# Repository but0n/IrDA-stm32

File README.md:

# 1. 绪论

## 1.1 红外遥控的发展

二十世纪, 刚步入八十年代, 电视产品在日本快速发展, 相应的红外遥控技术也在这里得到了广泛应用。为了实现遥控码的发射, 他们使用了一种集成发射芯片, 这种芯片的特点是: 单一控制（内部预置固定编码的遥控器只能控制单一型号的电器）。

随着时代不断地进步, 在目前的日常家居生活里面, 一般家庭都会配置各种各样的家用电器, 相应的也会有各种各样的遥控器, 当需要遥控某一家用电器时, 需要从多个遥控器中选出特定的一个。当家用电器越来越多, 对应的遥控器也越来越多, 从众多的遥控器中选出所需要的遥控器也会更加麻烦, 过多的遥控器会占据相当一部分的家居空间, 也不方便整理。

针对这种情况, 人们便产生了一种想法: 是否可以用一只遥控器遥控所有家用电器[5]？答案是肯定的, 多用遥控器就此产生了, 这种遥控器的特点是: 遥控器里面预置了不止一套编码, 而是多套编码, 可供用户在不同场合选择不同模式。

伴随着科技的日新月异, 红外遥控技术和单片机技术已经越来越成熟, 嵌入式技术的大力发展, 使大部分商家都在生产一种新的遥控器: 这种遥控器内置一个动态的编码库, 库内存放用户自主录入的编码, 使其具备一中心的功能——红外学习功能, 这种遥控器也有了新的名称: 学习型红外遥控器。

## 1.2 红外通信原理概述

所谓红外通信, 就是通过对二进制数字的调节与调制, 来进行信号传输, 红外通信接口就是红外信道的调制解调器。利用红外技术, 实现两点间的近距离保密通信和信息转发, 称为红外通信。它一般由两部分组成, 即: 红外发射系统与红外接收系统。单片机本身并不具备红外通信接口, 我们可以利用红外发射电路与红外接收电路组成一个应用于单片机的红外通信接口。

红外通信的基本原理是通过红外发射管发射的将基带二进制信号调制为一系列的脉冲串信号载波信号。

在红外通信过程中调制和发送的数据共有三种常用的协议:

 - NEC协议
 - 夏普协议
 - 索尼SIRC协议

其中应用最广泛的是NEC协议。NEC标准规定: 红外通信的载波频率为38KHz, 占空比为1: 3；数据格式包括了引导码、用户码、数据码和数据码反码, 编码总占 32 位。数据反码是 数据码反相后的编码, 编码时可用于对数据的纠错。注意: 第二段的用户码也可以在遥控应用电路中被设置成第一段用户码的反码, 如下图所示:

## 1.3 通用红外通信设备学码的实现

通用红外通信设备按照学习方式的不同可以分为两类:

 - 固定码格式的通信设备
 - 波形拷贝式的通信设备

第一种通信设备需要收集保存不同种类的红外设备信号, 然后识别比较, 最后再记录。这种红外设备的优点是硬件要求相对简易, 控制器的CPU频率可以较低；缺点是因为红外编码格式太多, 实现红外设备的成功复制比较难。

第二种通信设备是把原来红外设备发出的信号进行完全的复制, 不管原来红外设备红外信号是什么格式, 然后存储到非易失性的存储器(如EEPROM)中, 发送时再把保存的波形数据取出, 还原成原始信号。其优点是可以对任何一种红外设备进行学习；缺点是对控制器CPU的频率要求较高, RAM要大。
为了对尽可能多的设备进行控制, 本设计完成的是第二种红外通信设备。

# 2. 红外学码系统电路设计

上图是该硬件系统的完整电路图, 该电路共分为 7 个部分:

 1. 稳压电源电路
 2. 单片机启动配置电路
 3. 单片机外部时钟晶振电路
 4. 单片机上电复位电路
 5. 8 路学码部分电路
 6. 8 路发码部分电路
 7. 电路板接口电路

## 2.1 稳压电源电路

稳压电源电路是用来将外部供电电源的电压转换成单片机所需的 3.3V 稳定的电压。

这里使用了型号为 XC6206P332MR 的稳压 LDO 芯片, LDO即 Low Dropout Regulator, 是一种低压差线性稳压器。并且在芯片的电源输入引脚和电源输出引脚分别接了两个滤波电容, 用来防止电源可能发生的波动, 提高数字电路工作的稳健性。

上图是该 LDO 芯片型号为 P302MR 的典型输入输出电压曲线, 横轴为输入电压, 纵轴为输出电压, 通过上图可以清楚的看出, 我们所使用的 P332MR 当输入电压在 3.4V ~ 6V 的范围内, 都可以输出稳定的 3.3V 电压。

(这张图表是XC6206P302的数据, 官方的数据手册中只有该型号的图表作为一个典型示例, 没有我们所使用的 P332MR, 所以图表中的输出电压不是3.3V)

## 2.2 单片机启动配置电路

在STM32F10xxx里, 可以通过BOOT[1: 0]引脚选择三种不同启动模式:

- 从主闪存存储器启动:  主闪存存储器被映射到启动空间 (0x0000 0000), 但仍然能够在它原
有的地址 (0x0800 0000) 访问它, 即闪存存储器的内容可以在两个地址区域访问, 0x0000
0000 或 0x0800 0000。
> **以这种模式启动会运行用户烧写的程序**

- 从系统存储器启动: 系统存储器被映射到启动空间 (0x0000 0000), 但仍然能够在它原有的
地址(互联型产品原有地址为 0x1FFF B000, 其它产品原有地址为0x1FFF F000)访问它。
> **以这种模式启动会运行单片机出厂自带的 ISP 程序(In System Program 在系统编程), 这时我们可以通过串口连接单片机来上传程序。**

在系统复位后, SYSCLK 的第4个上升沿, BOOT 引脚的值将被锁存。用户可以通过设置 BOOT1
 和 BOOT0 引脚的状态, 来选择在复位后的启动模式。

在这次设计中, 我们将 BOOT1 通过一个 10K 的限流电阻直接接地, 通过 BOOT0 来控制单片机的启动模式。在实际使用的过程中, 单片机默认会以第一种模式启动 (BOOT0 悬空时为低电平), 也就是运行用户的程序, 如果我们要烧写程序, 只需要在单片机供电时确保 BOOT0 为高电平, 如下图, 将电阻 R3 右侧短接上方电容 C7 左侧即可。

## 2.3 单片机外部时钟晶振电路

4~16Mz外部振荡器可为系统提供更为精确的主时钟, 在这里单片机的高速外部时钟信号 (HSE) 是由以下一个8Mhz晶振产生的。
晶振两个引脚分别连接单片机的外部时钟引脚, 并且连接了两个 20pF 的负载电容, 作用是对晶体和振荡电路的补偿和匹配, 使电路易于起振并处于合理的激励态下, 同时对振荡频率也有一定的微调作用; 同时晶振也并联了一个 1M 欧的电阻 R2, 起到分流作用, 使晶振的工作电流在一个合理的范围内。

## 2.4 单片机上电复位电路

STM32 支持三种复位形式, 分别为系统复位、上电复位和备份区域复位, 这里的电路图属于上电复位。

芯片内部的复位信号源是单片机的 NRST 引脚, 脉冲发生器保证每一个(外部或内部)复位源都能有
至少20μs的脉冲延时; 当 NRST 引脚被拉低产生外部复位时, 它将产生复位脉冲, 然后单片机将会复位除了备份区域外的所有寄存器, 也就是清除上次运行后单片机配置可能发生的改变, 目的是让系统回到一个固定的初始状态, 这时所有寄存器的值都是已知的, 所以在这之后对单片机的每一次操作的结果都是可以判断的。

上图是单片机的上电复位电路, RESET 连接在单片机的 NRST 引脚, 在电路板开始供电时电容 C9 两侧是短路的, 也就是说这时 RESET 是直接接地的, 为低电平, 随着时间的推移, 电容将会被上拉的限流电阻 R8 充电, 随后 RESET 到 GND 之间就会形成断路, 这时 RESET 会变为高电平, 在整个过程也就中产生了低电平的复位信号。

## 2.5 8路学码部分电路

上图为 8 路的学码电路, 每一路都连接了一个 VS838 红外接收管:

VS838 的电源管脚 VCC 通过一个限流电阻接电源。

VS838 的 OUT 管脚是信号输出管脚, 当 VS838 接受到红外信号时 OUT 管脚会由高电平变为低电平, 直到红外信号消失。(未收到红外信号时 OUT 脚一直为高电平)

红外信号输出管脚是单片机获取红外信号的唯一来源, 所以该管脚连接在单片机的 GPIO 上, 当收到红外信号时该管脚产生的电平下降沿会被单片机的 GPIO 捕获并产生外部中断, 在中断函数中我们会记录该波形也就是红外信号的波形长度, 从而进行学码。

## 2.6 8路发码部分电路

上图为 8 路的发码电路, NEC标准规定:  红外通信的载波频率为38KHz, 占空比为1: 3,

这里我们使用单片机定时器的 PWM 输出功能产生所需的 38KHz 1: 3 波形, 通过对 PWM 输出的打开和关闭来实现载波。PWM 信号管脚通过一个限流电阻连接一个 NPN 三极管的, 通过控制三极管来打开和关闭红外 LED 进行红外信号的发送。

PWM 信号分别由单片机 TIM3 的四个通道和 TIM4 的四个通道产生。

## 2.7 电路板接口电路

该电路板的接口共有 4 个针脚:

 - 外部电源供电正极
 - 外部电源供电负极
 - 串口信号线 TX
 - 串口信号线 RX

 串口以其通信电路简单、可靠性高和传输距离远等优点，广泛应用在计算机与外设之间的通信电路中。

在本次设计中的串口有两个作用:
 - 串口控制:  电脑通过串口与电路板连接, 发送指令以控制单片机进行学码和发码操作
 - ISP:  电脑通过串口连接单片机来烧写程序。

# 3. 串口控制的8路学码系统的软件原理

## 3.1 主函数
```c
int main() {
	// 配置中断优先级分组
	NVIC_SetPriorityGrouping(0x07 - NVIC_GROUPING);

	uart_init(72, 115200);	// 初始化串口, 波特率为115200
	irda_init();			// irda初始化
	while(1) {
		// uart_sendStr("Alive~");
		// UART_CR();
		// delay_ms(1000);
	}
	return 0;
}
```
在系统供电之后单片机会进行下面这些操作:
- 配置中断优先级分组
- 串口功能初始化
- 8路红外发码收码系统的初始化
- 死循环, 等待用户的进一步操作

## 3.2 配置中断优先级分组

该系统的主要功能如串口控制、红外信号的捕获都依赖于单片机中的中断功能, 所以在程序启动后我们首先要做的就是单片机中断相关的配置。

STM32单片机使用的 Cortex-M3 内核中搭载了一个中断响应系统, 支持为数众多的系统异常和外部中断。当系统存在多个中断时, 优先级对于中断来说就很关键了, 它会决定一个中断是否能被掩蔽, 以及在未掩蔽的
情况下何时可以响应。优先级的数值越小, 则优先级越高。CM3 支持中断嵌套, 使得高优先级中断
会抢占 (preempt) 低优先级中断。有 3 个系统异常: 复位, NMI 以及硬 fault, 它们有固定的优先
级, 并且它们的优先级号是负数, 从而高于所有其它异常。所有其它异常的优先级则都是可编程的。

为了使抢占机能变得更可控, CM3 还把 256 级优先级按位分成高低两段, 分别称
为抢占优先级和子优先级。

并且在 NVIC 中有一个寄存器是 “应用程序中断及复位控制寄存器” (AIRCR), 它里面有一个位段名为 “优先级组”。该位段的值对每一个优先级可配置的异常都有影响 —— 把其优先级分为 2 个
位段: MSB 所在的位段（左边的）对应抢占优先级, 而 LSB 所在的位段（右边的）对应子优先级。

下图是应用程序中断及复位控制寄存器 (AIRCR) 地址:  0xE000_ED0C 的详细说明

我们所使用的 STM32 单片机的 PRIGROUP 只是用了4bit来表示:

通过上图我们可以得到一个规律, 即 PRIGROUP 的值等于 0x07 - 优先级组别。

在主函数中我们会通过下面这行语句将中断优先级分组设置为3, 在寄存器中:  xxx.y (x 指抢占式优先级, y 指响应式优先级):

```c
#define NVIC_GROUPING	3

NVIC_SetPriorityGrouping(0x07 - NVIC_GROUPING);
```

其中调用了 NVIC_SetPriorityGrouping 函数, 该函数用来设置 AIRCR 寄存器的 PPRIGROUP 位, 该函数的定义位于 STM32 官方的头文件 core_cm3.h 中:

```c
/* \brief  Set Priority Grouping

  The function sets the priority grouping field using the required unlock sequence.
  The parameter PriorityGroup is assigned to the field SCB->AIRCR [10: 8] PRIGROUP field.
  Only values from 0..7 are used.
  In case of a conflict between priority grouping and available
  priority bits (__NVIC_PRIO_BITS), the smallest possible priority group is set.

    \param [in]      PriorityGroup  Priority grouping field.
 */
__STATIC_INLINE void NVIC_SetPriorityGrouping(uint32_t PriorityGroup)
{
	uint32_t reg_value;
	uint32_t PriorityGroupTmp = (PriorityGroup & (uint32_t)0x07);
	// only values 0..7 are used

	reg_value  =  SCB->AIRCR;
	// read old register configuration
	reg_value &= ~(SCB_AIRCR_VECTKEY_Msk | SCB_AIRCR_PRIGROUP_Msk);
	// clear bits to change
	reg_value  =  (reg_value |
		((uint32_t)0x5FA << SCB_AIRCR_VECTKEY_Pos) |
        (PriorityGroupTmp << 8));
	// Insert write key and priorty group
	SCB->AIRCR =  reg_value;
}
```

## 3.3 串口功能初始化

STM32 中的通用同步异步收发器(USART)提供了一种灵活的方法与使用工业标准NRZ异步串行数据格式的
外部设备之间进行全双工数据交换。USART利用分数波特率发生器提供宽范围的波特率选择。
它支持同步单向通信和半双工单线通信，也支持LIN(局部互连网)，智能卡协议和IrDA(红外数据
组织)SIR ENDEC规范，以及调制解调器(CTS/RTS)操作。它还允许多处理器通信。
使用多缓冲器配置的DMA方式，可以实现高速数据通信。

在配置好中断优先级分组后, 会进行单片机 USART1 串口的初始化, 配置其波特率为 115200, 并打开串口中断:

```c
uart_init(72, 115200);	// 初始化串口, 波特率为115200
```

下面是该函数的定义:

```c
void uart_init(unsigned int pclk2, unsigned int bound) {
    float temp;
    unsigned short mantissa;
    unsigned short fraction;
    temp = (float)(pclk2*1000000)/(bound*16);
    mantissa = temp;
    fraction = (temp - mantissa) * 16;
    mantissa <<= 4;
    mantissa += fraction;
    RCC->APB2ENR |= RCC_APB2ENR_IOPAEN;		// 打开 GPIOA 时钟
    RCC->APB2ENR |= RCC_APB2ENR_USART1EN;	// 打开 USART1 时钟

    GPIOA->CRH &= 0xFFFFF00F;				// USART GPIO 引脚配置
    GPIOA->CRH |= 0x000008B0;

    RCC->APB2RSTR |= RCC_APB2RSTR_USART1RST;
    RCC->APB2RSTR &= ~RCC_APB2RSTR_USART1RST;

    USART1->BRR = mantissa;
    USART1->CR1 |= 0x200C;	//设置 UE, TE and RE

    USART1->CR1 |= 1<<8;	//PE 中断使能
    USART1->CR1 |= 1<<5;	//RX 非空中断使能

    USART1->SR;     // 读取 SR 寄存器以将 TXE 和 TE 位清零,(复位值:  0x00C0)

	// SCB->AIRCR &= 0x05FAF8FF;	// AIRCE Key:  0x05FA
	// SCB->AIRCR |= 0x05FA0400;	// Set up group value
	NVIC_EnableIRQ(USART1_IRQn);	// 使能串口中断
	NVIC_SetPriority(USART1_IRQn, 0b1001);//设置其优先级
}
```

该函数会进行下面这些操作:
- 打开 USART1 和 USART1 所使用的 GPIO 的时钟, 由于 STM32 的低功耗设计, 只有在打开时钟后才能操作对应的外设。
- 配置 GPIO 引脚:

	在本次设计中我们使用的串口是全双工模式的, 所以根据上图要求, TX 应该配置为推挽复用输出, RX 应该配置为浮空输入或上拉输入。其中 GPIO 引脚的配置需要操作 CRL 或 CRH 寄存器, 下图是该寄存器的说明:

	通过上表我们可以看到, 推挽复用输出的值为 0b1000 (0x8), 上拉输入的值为 0b1011 (0xB), 所以就有了下面这两行配置代码:
	```c
	GPIOA->CRH &= 0xFFFFF00F;				// USART GPIO 引脚配置
	GPIOA->CRH |= 0x000008B0;
	```
- 复位并配置串口1相关寄存器
- 使能单片机的串口中断, 当单片机收到用户从电脑发送的字符后,  会触发串口中断并执行下面的中断处理函数 USART1_IRQHandler :

```c
void USART1_IRQHandler(void) {
	if(USART1->SR & USART_SR_RXNE) {
		const char cmd = USART1->DR;	// 读取串口接收寄存器来清除 RXNE 标志
		switch (cmd) {
			case 0x0D: 	//回车键
			case 0x0A:
				uart_sendStr("\n\r当前命令: \t");
				uart_sendStr(gCmdCache);
				UART_CR();
				uart_decode(gCmdCache);
				clrCache();
				break;
			case 0x08: 	//退格键
			case 0x7F:
				if(top>=0) {		// 防止指针跨域操作, 否则多次按退格键会出现bug
					pop = '\0';
					uart_sendData(0x7F);
					uart_sendData(0x08);
				}
				break;
			case TOKEN_START: 	//$ - 命令起始标志
				clrCache();
			default: 	//其它按键
				if(STACK_OVERFLOW)	//如果指令缓存将要溢出, 则不会入栈当前字符
					break;
				push(cmd);			//保存当前字符
				uart_sendData(cmd);	//在终端回显, 反馈用户输入的字符
				break;
		}
	}
}
```

我们将用户的输入分为四种:
- 串口命令的起始标志:  $
- 普通字符, 比如字母和数字
- 回车键
- 删除键

在上面的源码中可以清楚的看到, 当单片机收到第一种输入也就是 '$' 时, 单片机会清空用于记录串口控制指令的数组。

当单片机收到第二种输入时, 单片机会记录并保存用户当前输入的字符到用于记录串口指令的数组中, 并把当前字符通过串口发送给电脑, 也就是在终端中反馈给用户。

当单片机收到第三种输入即回车键时, 单片机会通过调用 uart_decode 函数来解析当前指令并执行相应的操作。

当单片机收到第四种输入即删除键时, 单片机会在串口控制指令数组中删除最后的一个字符, 并且通过串口输出删除键的键值, 以删除电脑终端上的字符, 这样就实现了删除字符的功能。

### 3.3.1 串口控制指令的规则定义

我们在头文件 uart.h 中实现了串口指令的规则的宏定义:

```c
#define TOKEN_START		'$'
#define TOKEN_SEND		'S'
#define TOKEN_LEARN		'L'
#define TOKEN_OFFSET		0x01
#define CMD_NUM_MAX		'8'
#define CMD_NUM_MIN		'1'
#define ISLEGAL_NUM(k)	(((k) >= CMD_NUM_MIN) && ((k) <= CMD_NUM_MAX))
```

在规则中定义了下面三种特殊标志:

- $ 字符作为串口指令的起始标志, 当用户输入 $ 时意味着一条指令的开始, 在 $ 之前输入的所有字符都将被删除, 在 $ 之后输入的所有字符都将作为串口指令被记录;

- **S** (Send)字符作为红外发码指令的标志, 该标志应当紧随着命令起始标志 $, 例如:
 - $S1 - 1号红外外设执行发码操作
 - $S123 - 1号、2号、3号外设执行发码操作
 - $S85 - 8号、5号外设执行发码操作

- **L** (Learn)字符作为红外收码状态切换 (Toggle) 指令, 状态切换指的是如果被操作外设的收码状态是关闭的则执行该指令后会被打开, 如果是打开的则会被关闭, 同样该标志也要紧随着命令起始标志 $, 例如:
 - $L2 - 2号红外外设收码状态切换
 - $L345 - 3号、4号、5号红外外设收码状态切换

在规则中定义了操作标志 S 和 L 在指令中的偏移值, 当前的规则是操作标志的位置必须在指令的第二个字符, 也就是紧随起始标志之后。

在规则中定义了指令中可能出现的数字的最大值以及最小值, 以限制数字的合法范围, 防止非法指令造成的越界操作, 提高该系统的稳健性。该范围取决于本系统的红外外设数量, 在这里我们共有8路外设, 所以其合法范围是 1 到 8。

### 3.3.2 串口控制指令的解析

当用户在终端中键入回车键意味着一条指令的结束, 这时该指令会通过 uart_decode 函数来进行解析, 该函数的定义在 uart.c 文件中, 下面是该函数的源码:

```c
void uart_decode(char *token) {
	if(*token == 0)
		return;	//如果发生越界则结束 decode
	if(ISLEGAL_NUM(*token)) {//如果当前操作符为效数字

		uart_sendStr(" - ");
		uart_sendData(*token);//在终端显示当前处理的学码电路通道号
		// 如果这条指令是学码命令
		if(gCmdCache[TOKEN_OFFSET] == TOKEN_LEARN) {
			// (Toggle between enable and disable) 如果该路学码中断是关闭的则使能, 反之则关闭
			*g_IrDA_Device[*token - '1'].IrInterrup ^= 1;
			uart_sendStr("号: 学码");
			uart_sendStr(*g_IrDA_Device[*token - '1'].IrInterrup?"开启\n\r": "关闭\n\r");
		}
		else if(gCmdCache[TOKEN_OFFSET] == TOKEN_SEND) {// 如果这条指令是发码命令
			uart_sendStr("号: 发码开启\n\r");
			// 在发码的过程中为了防止自发自收, 得确保所有的接收中断都是关闭的, 否则中断会干扰发送
			*g_IrDA_Device[0].IrInterrup =
				*g_IrDA_Device[1].IrInterrup =
				*g_IrDA_Device[2].IrInterrup =
				*g_IrDA_Device[3].IrInterrup =
				*g_IrDA_Device[4].IrInterrup =
				*g_IrDA_Device[5].IrInterrup =
				*g_IrDA_Device[6].IrInterrup =
				*g_IrDA_Device[7].IrInterrup = 0;
			irda_encode(&g_IrDA_Device[*token - '1']);//发码
		}
	}
	uart_decode(++token);
}

```

从上面的代码中我们不难看出, 该函数一次只判断一次字符, 当该字符为合法数字时根据当前指令中的操作标志对该数字代表的外设执行相应的操作, 然后再次调用该函数, 处理下一个字符, 以实现对当前串口指令中每一个字符的遍历。

## 3.4 八路红外发码收码系统的初始化

```c
void irda_init() {
	irda_PWM_Init();	// 发送功能初始化
	irda_EXTI_Init();	// 接收功能初始化

	//实例化红外外设对象 - 第 1 路
	g_IrDA_Device[0].IrInterrup	= BIT_ADDRP(&(EXTI->IMR), 0);
	g_IrDA_Device[0].IrPWM		= BIT_ADDRP(&(TIM3->CCER), 0);
	g_IrDA_Device[0].signal		= BIT_ADDRP(&(GPIOC->IDR), 0);

	//实例化红外外设对象 - 第 2 路
	g_IrDA_Device[1].IrInterrup	= BIT_ADDRP(&(EXTI->IMR), 1);
	g_IrDA_Device[1].IrPWM		= BIT_ADDRP(&(TIM3->CCER), 4);
	g_IrDA_Device[1].signal		= BIT_ADDRP(&(GPIOC->IDR), 1);

	//实例化红外外设对象 - 第 3 路
	g_IrDA_Device[2].IrInterrup	= BIT_ADDRP(&(EXTI->IMR), 2);
	g_IrDA_Device[2].IrPWM		= BIT_ADDRP(&(TIM3->CCER), 8);
	g_IrDA_Device[2].signal		= BIT_ADDRP(&(GPIOC->IDR), 2);

	//实例化红外外设对象 - 第 4 路
	g_IrDA_Device[3].IrInterrup	= BIT_ADDRP(&(EXTI->IMR), 3);
	g_IrDA_Device[3].IrPWM		= BIT_ADDRP(&(TIM3->CCER), 12);
	g_IrDA_Device[3].signal		= BIT_ADDRP(&(GPIOC->IDR), 3);

	//实例化红外外设对象 - 第 5 路
	g_IrDA_Device[4].IrInterrup	= BIT_ADDRP(&(EXTI->IMR), 6);
	g_IrDA_Device[4].IrPWM		= BIT_ADDRP(&(TIM4->CCER), 0);
	g_IrDA_Device[4].signal		= BIT_ADDRP(&(GPIOC->IDR), 6);

	//实例化红外外设对象 - 第 6 路
	g_IrDA_Device[5].IrInterrup	= BIT_ADDRP(&(EXTI->IMR), 7);
	g_IrDA_Device[5].IrPWM		= BIT_ADDRP(&(TIM4->CCER), 4);
	g_IrDA_Device[5].signal		= BIT_ADDRP(&(GPIOC->IDR), 7);

	//实例化红外外设对象 - 第 7 路
	g_IrDA_Device[6].IrInterrup	= BIT_ADDRP(&(EXTI->IMR), 8);
	g_IrDA_Device[6].IrPWM		= BIT_ADDRP(&(TIM4->CCER), 8);
	g_IrDA_Device[6].signal		= BIT_ADDRP(&(GPIOC->IDR), 8);

	//实例化红外外设对象 - 第 8 路
	g_IrDA_Device[7].IrInterrup	= BIT_ADDRP(&(EXTI->IMR), 9);
	g_IrDA_Device[7].IrPWM		= BIT_ADDRP(&(TIM4->CCER), 12);
	g_IrDA_Device[7].signal		= BIT_ADDRP(&(GPIOC->IDR), 9);
}
```

上面是红外外设初始化函数, 该函数执行了下面几个操作:
- 发码功能初始化, 也就是 PWM 初始化
- 收码功能初始化, 也就是外部中断初始化
- 分别实例化 8 路红外外设对象

### 3.4.1 发码功能初始化

```c
//红外学码电路发码部分初始化函数
void irda_PWM_Init() {
	// 红外发射管分别依次连接在单片机的 TIM3_CH1, TIM3_CH2, TIM3_CH3, TIM3_CH4,
	//		TIM4_CH1, TIM4_CH2, TIM4_CH3, TIM4_CH4
	//	所以在这个函数中需要初始化 TIM3 和 TIM4

    RCC->APB1ENR |= RCC_APB1ENR_TIM3EN | RCC_APB1ENR_TIM4EN;	//TIM3 Enable
    RCC->APB2ENR |= RCC_APB2ENR_IOPAEN | RCC_APB2ENR_IOPBEN;	//IO Port A and B Enable

	// GPIOA GPIOB 寄存器配置
    GPIOA->CRL &= 0x00FFFFFF;
    GPIOA->CRL |= 0xBB000000;   //将 6, 7 脚配置为复用推挽输出
    GPIOA->ODR |= 1<<7;			//TIM3_CH2 GPIO 配置
    GPIOA->ODR |= 1<<6;			//TIM3_CH1 GPIO 配置

    GPIOB->CRL &= 0x00FFFF00;
    GPIOB->CRL |= 0xBB0000BB;	//将 0, 1, 6, 7 脚配置为复用推挽输出

	GPIOB->CRH &= 0xFFFFFF00;
	GPIOB->CRH |= 0x000000BB;	//将 8, 9 脚配置为复用推挽输出

	GPIOB->ODR |= 1<<0 | 1<<1 | 1<<6 | 1<<7 | 1<<8 | 1<<9;

	// TIM3 寄存器配置
    TIM3->ARR = IR_PWM_ARR - 1;	//配置计数器最大值
    TIM3->PSC = IR_PWM_PSC - 1;	//配置计数器分频

    TIM3->CCMR1 |= 6<<4;			//CH1 设置为 OC1M[2: 0]:  PWM 模式
    TIM3->CCMR1 |= TIM_CCMR1_OC1PE;	//CH1 设置为 OC1PE:  使能
    TIM3->CCMR1 |= 6<<12;   		//CH2 设置为 OC2M[2: 0]:  PWM 模式
    TIM3->CCMR1 |= TIM_CCMR1_OC2PE;	//CH2 设置为 OC2PE:  使能
    TIM3->CCMR2 |= 6<<4;    		//CH3 设置为 OC3M[2: 0]:  PWM 模式
    TIM3->CCMR2 |= TIM_CCMR2_OC3PE;	//CH3
    TIM3->CCMR2 |= 6<<12;			//CH4
    TIM3->CCMR2 |= TIM_CCMR2_OC4PE;	//CH4

	TIM3->CCR1 = TIM3->CCR2 = TIM3->CCR3 = TIM3->CCR4 = IR_PWM_CCR_DEF;
	//CH1 ~ CH4 计数器使能
    // TIM3->CCER |= TIM_CCER_CC1E | TIM_CCER_CC2E | TIM_CCER_CC3E | TIM_CCER_CC4E;

    TIM3->CR1 |= TIM_CR1_ARPE | TIM_CR1_CEN;	//配置APRE位并使能计数器

	// TIM4 寄存器配置
    TIM4->ARR = IR_PWM_ARR - 1;	//配置计数器最大值
    TIM4->PSC = IR_PWM_PSC - 1;	//配置计数器分频

    TIM4->CCMR1 |= 6<<4;			//CH1 设置为 OC1M[2: 0]:  PWM 模式
    TIM4->CCMR1 |= TIM_CCMR1_OC1PE;	//CH1 设置为 OC1PE:  使能
    TIM4->CCMR1 |= 6<<12;   		//CH2 设置为 OC2M[2: 0]:  PWM 模式
    TIM4->CCMR1 |= TIM_CCMR1_OC2PE;	//CH2 设置为 OC2PE:  使能
    TIM4->CCMR2 |= 6<<4;    		//CH3 设置为 OC3M[2: 0]:  PWM 模式
    TIM4->CCMR2 |= TIM_CCMR2_OC3PE;	//CH3
    TIM4->CCMR2 |= 6<<12;			//CH4
    TIM4->CCMR2 |= TIM_CCMR2_OC4PE;	//CH4

	TIM4->CCR1 = TIM4->CCR2 = TIM4->CCR3 = TIM4->CCR4 = IR_PWM_CCR_DEF;
	//CH1 ~ CH4 计数器使能
    // TIM4->CCER |= TIM_CCER_CC1E | TIM_CCER_CC2E | TIM_CCER_CC3E | TIM_CCER_CC4E;

    TIM4->CR1 |= TIM_CR1_ARPE | TIM_CR1_CEN;	//配置APRE位并使能计数器
}
```

红外发射管分别依次连接在单片机的 TIM3_CH1、TIM3_CH2、TIM3_CH3、TIM3_CH4、TIM4_CH1、TIM4_CH2、TIM4_CH3、TIM4_CH4, 所以在这个函数中初始化了 TIM3 和 TIM4 的 PWM 输出功能, 并且按照 NEC 协议标准将其 PWM 配置为 38KHz 1: 3占空比。

### 3.4.2 收码功能初始化

```c
//红外学码电路收码部分初始化函数
void irda_EXTI_Init() {
	//使能外部中断
	NVIC_EnableIRQ(EXTI0_IRQn);
	NVIC_EnableIRQ(EXTI1_IRQn);
	NVIC_EnableIRQ(EXTI2_IRQn);
	NVIC_EnableIRQ(EXTI3_IRQn);
	NVIC_EnableIRQ(EXTI9_5_IRQn);

	NVIC_SetPriority(EXTI0_IRQn, 0b0011);	//设置中断优先级
	NVIC_SetPriority(EXTI1_IRQn, 0b0011);	//设置中断优先级
	NVIC_SetPriority(EXTI2_IRQn, 0b0011);	//设置中断优先级
	NVIC_SetPriority(EXTI3_IRQn, 0b0011);	//设置中断优先级
	NVIC_SetPriority(EXTI9_5_IRQn, 0b0011);	//设置中断优先级

	// 红外接收管的数据输出分别连接在单片机GPIO端口 C 的0, 1, 2, 3, 6, 7, 8, 9 引脚

	RCC->APB2ENR |= RCC_APB2ENR_AFIOEN;	//使能 AFIO 时钟, 因为中断属于复用功能
	RCC->APB2ENR |= RCC_APB2ENR_IOPCEN;	//使能 IO Port C 时钟
//					76543210
	GPIOC->CRL &= 0x00FF0000;	//清空 0, 1, 2, 3, 6, 7
	GPIOC->CRL |= 0x88008888;	//配置为输入模式

	GPIOC->CRH &= 0xFFFFFF00;	//清空 8, 9
	GPIOC->CRH |= 0x00000088;	//配置为输入模式

	GPIOC->ODR |= 1 | 1<<1 | 1<<2 | 1<<3 | 1<<6 | 1<<7 | 1<<8 | 1<<9;	//上拉电阻

	AFIO->EXTICR[0] = 0x2222;	//使能C端口 0, 1, 2, 3 引脚的中断复用
	AFIO->EXTICR[1] = 0x2200;	//使能C端口 6, 7 引脚的中断复用
	AFIO->EXTICR[2] = 0x0022;	//使能C端口 8, 9 引脚的中断复用

	EXTI->FTSR |= 1 | 1<<1 | 1<<2 | 1<<3 | 1<<6 | 1<<7 | 1<<8 | 1<<9;
	//下降沿触发
	EXTI->RTSR |= 1 | 1<<1 | 1<<2 | 1<<3 | 1<<6 | 1<<7 | 1<<8 | 1<<9;
	//上升沿触发
}
```
红外接收管的数据输出分别连接在单片机GPIO端口 C 的0, 1, 2, 3, 6, 7, 8, 9 引脚, 该函数配置了相应管脚的外部中断, 当收码状态被用户通过串口指令设置为打开后, 如果该路的红外接收管收到红外信号则会产生下降沿然后会被单片机捕获并执行相应的中断处理函数。

下面的源码是各路中断处理函数的定义:

```c
//各路的中断处理函数
void EXTI0_IRQHandler(void) {
	IRQ_HANDLE_CORE(0);
	EXTI->PR |= 1<<0;
}

void EXTI1_IRQHandler(void) {
	IRQ_HANDLE_CORE(1);
	EXTI->PR |= 1<<1;
}

void EXTI2_IRQHandler(void) {
	IRQ_HANDLE_CORE(2);
	EXTI->PR |= 1<<2;
}

void EXTI3_IRQHandler(void) {
	IRQ_HANDLE_CORE(3);
	EXTI->PR |= 1<<3;
}

void EXTI9_5_IRQHandler(void) {
	unsigned long origin = EXTI->PR;

	if(origin & EXTI_PR_PR6) {			//如果来源为 6
		IRQ_HANDLE_CORE(4);
		EXTI->PR |= 1<<6;
	} else if(origin & EXTI_PR_PR7) {	//如果来源为 7
		IRQ_HANDLE_CORE(5);
		EXTI->PR |= 1<<7;
	} else if(origin & EXTI_PR_PR8) {	//如果来源为 8
		IRQ_HANDLE_CORE(6);
		EXTI->PR |= 1<<8;
	} else if(origin & EXTI_PR_PR9) {	//如果来源为 9
		IRQ_HANDLE_CORE(7);
		EXTI->PR |= 1<<9;
	}
}
```

可以看出当每一路都调用了一个名为 IRQ_HANDLE_CORE() 的宏, 也可以称作内联函数, 是在头文件 irda.h 中声明的:

```c
#define IRQ_HANDLE_CORE(i) do {\
	*g_IrDA_Device[(i)].IrInterrup = 0;\
	irda_decode(&g_IrDA_Device[(i)]);\
	\
	IR_WAVE_FEEDBACK((i));\
	\
	UART_CR();\
} while(0)
```
*i为被控制的外设号码*

在上面的定义中, 该内联函数先关闭被操作外设的外部中断, 防止在学码过程中被打断, 然后执行 irda_decode 函数来执行学码操作, 最后执行 IR_WAVE_FEEDBACK 在终端将解析到的红外波形数据在终端中反馈给用户。

### 3.4.3 红外外设对象初始化

本次设计中使用面对对象的思维方式, 通过C语言的结构体 (struct) 来实现红外外设对象的封装, 通过这种方法可以增加代码可读性, 提高执行效率。

```c
#define IR_DEVICES_NUM			8		//共有8路学码发码外设
#define WAVE_SEGMEENT_NUM		400		//红外波形共有200次电平翻转

typedef struct {
	unsigned short token[WAVE_SEGMEENT_NUM];
	//保存红外波形的数组
	volatile unsigned long *IrInterrup;
	//指针指向中断使能寄存器的某一位 (位带操作), 用来打开和关闭当前中断
	volatile unsigned long *IrPWM;
	//指针指向 PWM 使能寄存器的某一位 (位带操作), 用来打开和关闭 PWM
	volatile unsigned long *signal;
	//指针指向 GPIO ODR 的某一位, 用来检测输入红外波形的高低
} ir_st, *ir_pst;
ir_st g_IrDA_Device[IR_DEVICES_NUM];
```

**这里定义了一个全局变量, 用来存储 8 红外外设对象**, 并在红外发码收码系统初始化函数中对其赋值:

```c
//实例化红外外设对象 - 第 1 路
g_IrDA_Device[0].IrInterrup	= BIT_ADDRP(&(EXTI->IMR), 0);
g_IrDA_Device[0].IrPWM		= BIT_ADDRP(&(TIM3->CCER), 0);
g_IrDA_Device[0].signal		= BIT_ADDRP(&(GPIOC->IDR), 0);

//实例化红外外设对象 - 第 2 路
g_IrDA_Device[1].IrInterrup	= BIT_ADDRP(&(EXTI->IMR), 1);
g_IrDA_Device[1].IrPWM		= BIT_ADDRP(&(TIM3->CCER), 4);
g_IrDA_Device[1].signal		= BIT_ADDRP(&(GPIOC->IDR), 1);

//实例化红外外设对象 - 第 3 路
g_IrDA_Device[2].IrInterrup	= BIT_ADDRP(&(EXTI->IMR), 2);
g_IrDA_Device[2].IrPWM		= BIT_ADDRP(&(TIM3->CCER), 8);
g_IrDA_Device[2].signal		= BIT_ADDRP(&(GPIOC->IDR), 2);

//实例化红外外设对象 - 第 4 路
g_IrDA_Device[3].IrInterrup	= BIT_ADDRP(&(EXTI->IMR), 3);
g_IrDA_Device[3].IrPWM		= BIT_ADDRP(&(TIM3->CCER), 12);
g_IrDA_Device[3].signal		= BIT_ADDRP(&(GPIOC->IDR), 3);

//实例化红外外设对象 - 第 5 路
g_IrDA_Device[4].IrInterrup	= BIT_ADDRP(&(EXTI->IMR), 6);
g_IrDA_Device[4].IrPWM		= BIT_ADDRP(&(TIM4->CCER), 0);
g_IrDA_Device[4].signal		= BIT_ADDRP(&(GPIOC->IDR), 6);

//实例化红外外设对象 - 第 6 路
g_IrDA_Device[5].IrInterrup	= BIT_ADDRP(&(EXTI->IMR), 7);
g_IrDA_Device[5].IrPWM		= BIT_ADDRP(&(TIM4->CCER), 4);
g_IrDA_Device[5].signal		= BIT_ADDRP(&(GPIOC->IDR), 7);

//实例化红外外设对象 - 第 7 路
g_IrDA_Device[6].IrInterrup	= BIT_ADDRP(&(EXTI->IMR), 8);
g_IrDA_Device[6].IrPWM		= BIT_ADDRP(&(TIM4->CCER), 8);
g_IrDA_Device[6].signal		= BIT_ADDRP(&(GPIOC->IDR), 8);

//实例化红外外设对象 - 第 8 路
g_IrDA_Device[7].IrInterrup	= BIT_ADDRP(&(EXTI->IMR), 9);
g_IrDA_Device[7].IrPWM		= BIT_ADDRP(&(TIM4->CCER), 12);
g_IrDA_Device[7].signal		= BIT_ADDRP(&(GPIOC->IDR), 9);
```

## 3.5 学码函数

```c
//红外信号学码函数
void irda_decode(ir_pst ir) {
	unsigned char lastStatus = *ir->signal;
	//用来保存上一次电平状态, 以判断电平是否发生翻转
	unsigned short *wave = ir->token;
	//指向用来存储波形长度数据的数组

	for(unsigned int cnt = 0; cnt < WAVE_SEGEMENT_LENGTH; cnt++) {
		//计数器递增, 计数器的数值代表波形长度
		if(lastStatus != *ir->signal) {
			*wave++ = cnt;//当发生电平跳转时保存当前计数并将指针指向波形数组的下一个元素
			if(IR_ISOVERFLOW(wave, ir->token)) {
				//如果遥控器按键未松开会导致多次发送红外信号
				uart_sendStr("\n\r波形数据溢出, 请松开按键!\n\r");
				return;
			}
			cnt = 0;	//清空计数器以便于测量下一段波形长度
		}
		lastStatus = *ir->signal;
		delay_us(26);	// 跳过38KHz载波信号的电平反转
	}
	*wave = 0;			// 数据结束标志
	unsigned short len = wave - ir->token;
	//计算波形的高电平和低电平共有多少段
	uart_sendStr("\n\r波形数组长度: \t");
	uart_short2char(len);//在终端反馈数据
	UART_CR();
}
```

本次设计采用的学码方式是波形拷贝式, 也就是通过记录接收到的红外波形的低电平和高电平的电平宽度, 对红外信号进行完全的复制。

## 3.6 发码函数

```c
//红外信号发码函数
void irda_encode(ir_pst ir) {
	unsigned short *wave = ir->token;//定义一个指针指向被发送的波形数据
	unsigned short cnt;//计数器
	while((cnt = *wave++)) {//提取当前波形长度, 如果长度值有效则将发送波形, 并且将 wave 指向下一段数据
		*ir->IrPWM ^= 1;	//电平翻转,切换 PWM 输出状态,如果之前输出是打开的则关闭, 如果之前是关闭的则打开
		while(cnt--)
			delay_us(26);	//计数器单位为 20us, 因为波形有38KHz载波
	}
	*ir->IrPWM = 0;//发码结束后关闭 PWM 输出
}
```
**
发码函数中通过学码函数记录的数据, 对 PWM 进行打开和关闭来实现载波的发送。由于这里的计数器和学码电路中保存数据的时间单位同为 26 微秒, 所以发送的红外信号和接收到的红外信号几乎是完全相同的, 从而实现了红外信号的学码功能。

# 4. 总结

## 4.1 本设计的软件使用说明

### 4.1.1 软件开发环境

本设计的软件系统环境为 Linux 系统, 使用了如下 GNU 工具:
- Makefile
- arm-none-eabi-gcc
- stm32flash (用来通过串口给单片机烧写程序)

### 4.1.2 源码文件框架

```
├── Makefile
├── Makefile.common
├── libs
│   ├── Makefile
│   ├── STM32_USB-FS-Device_Lib_V4.0.0
│   │   ├── Libraries
│   │   ├── MCD-ST\ Liberty\ SW\ License\ Agreement\ V2.pdf
│   │   ├── Projects
│   │   ├── Release_Notes.html
│   │   ├── Utilities
│   │   └── _htmresc
│   ├── include
│   │   ├── bit.h
│   │   ├── irda.h
│   │   ├── tty.h
│   │   └── uart.h
│   └── source
│       ├── irda.c
│       └── uart.c
├── linker.ld
└── src
    ├── Makefile
    ├── main.c
    └── startup.c
```

上面是本设计的源码文件结构, 其中有:

- Makefile - 用来实现整个项目的自动化编译, 以及代码的烧写
- Makefile.common - Makefile 的配置文件, 类似于 C 语言中的头文件
- libs/STM32_USB-FS-Device_Lib_V4.0.0 文件夹 - 里面存储了 stm32 官方的库
- libs/include 文件夹 - 里面存储了本次设计的头文件 .h 文件
- libs/source 文件夹 - 里面存储了本次设计的源码 .c 文件
- linker.ld - 链接文件, 根据 stm32 RAM 和 Flash 的大小来定义, 编译时会通过该文件生成最终的二进制文件
- src 文件夹 - 里面是本次设计的主函数源码以及单片机的启动代码

### 4.1.3 软件使用说明

首先要确保在终端中当前的目录为项目文件内, 可以使用 `pwd` 命令查看当前路径, 使用 `cd` 命令 (Change Directory) 来进入当前项目文件。

- `make` 命令: 用来编译整个工程, 并且在当前目录中生成二进制文件 main.bin
- `make flash` 命令: 用来将二进制文件 main.bin 通过 USB 烧写到单片机
- `make clean` 命令: 清除编译产生的中间文件和目标文件

## 4.2 电路板的使用及功能演示

### 4.2.1 烧写程序

1. 按照 4.1.3 章节的软件说明, 使用 make 命令来生成用来被烧写的 main.bin 文件。

2. 按照电路板的接口旁的丝印信息, 将其通过杜邦线连接 串口转 USB 模块:

	- 电路板的 `+` 针脚连接串口转 USB 模块的 `+5V`
	- 电路板的 `-` 针脚连接串口转 USB 模块的 `GND`
	- 电路板的 `T` 针脚连接串口转 USB 模块的 `RXD`
	- 电路板的 `R` 针脚连接串口转 USB 模块的 `TXD`

3. 按照 2.2 章节的启动配置说明, 将电路板上的电阻 R3 右侧短接上方电容 C7 左侧, 然后再将串口转 USB 模块连接电脑, 此时单片机会运行其出厂自带的 ISP 程序(In System Program 在系统编程), 这样我们才能通过串口连接单片机来上传程序

4. 按照 4.1.3 章节的说明使用 make flash 命令来烧写程序, 如果看到这样的信息说明程序烧写成功:

### 4.2.2 功能演示

在进行功能演示之前, 需要使用下列步骤在电路板和电脑之间建立串口通信:

1. 将已烧写过程序的两个电路板通过串口转 USB 模块分别连接到电脑

2. 在终端键入 `ls -al /dev/`

3. 在反馈的信息中寻找 `tty.SLAB_USBtoUART` 和 `tty.SLAB_USBtoUARTxxx` (xxx为若干个数字), 这两个设备分别对应着刚才连接的两个电路板。如果找到了这两个设备说明电路板已经成功连接。

4. 在终端键入 `screen /dev/设备名称 115200` 来建立串口通信

这时我们就可以使用串口来控制单片机了:

上图是学码演示, 在这次演示中我们输入了两条指令, 从反馈的信息中我们不难看出其指令是支持同时控制多路外设的, 并且体现除了 $L 命令效果, 即对状态的切换。当我们按下遥控器上的按钮时单片机收到了红外信号并对信号波形进行记录, 以实现对波形的学习。

上图是该系统对错误操作的处理, 当用户长时间按住遥控器按键会造成红外信号的重复发送, 这时单片机会停止学码, 并反馈信息给用户, 维护了系统的稳健性。

在发码演示中我们通过两个电路板进行测试, 在这里我们分别称作电路板 A 和电路板 B , 首先打开 A 电路板的学码功能, 然后使用电视遥控器发一个信号给该电路板, 然后我们在打开另一个电路板 B 的学码功能, 这时使用 A 电路板的发码功能发送它所记录的遥控器信号给 B 电路板, 这时通过对比 A B 收到的信号数据来检查学码功能。

下面是实际的操作反馈：

上图为两个电路板的串口通信界面, 其中一个学习了电视遥控器所发出的信号, 然后将该信号发送给另一个电路板, 通过对比两组波形信号, 可以看到波形数据十分吻合, 误差极小, 完成了学码功能。

# 5. 参考资料
- Cortex-M3 权威指南
- STM32F10xxx参考手册
- [4.23 STM32 外设篇-红外线接收工作原理及程序设计  此博文包含图片	(2015-06-10 15: 38: 33)](http: //blog.sina.com.cn/s/blog_8a4745370102vq8m.html)
- [浅谈38K红外发射接受编码](http: //www.voidcn.com/blog/u012993936/article/p-3554521.html)
- [基于STM32的学习型通用红外遥控设备的设计实现(1~3)](http: //blog.csdn.net/u013686019/article/details/19834441)
- [STM32学习之路-AIRCR寄存器PRIGROUP位的配置](http: //www.ithao123.cn/content-8377076.html)
- [ STM32学习笔记: 外部中断EXTI的使用](http: //blog.csdn.net/u010173859/article/details/10179627)
- [STM32学习笔记之EXTI（外部中断）](http: //blog.sina.com.cn/s/blog_6623834301018woa.html)
- [STM32中断优先级彻底讲解](https: //wenku.baidu.com/view/4944282c915f804d2b16c18e.html)

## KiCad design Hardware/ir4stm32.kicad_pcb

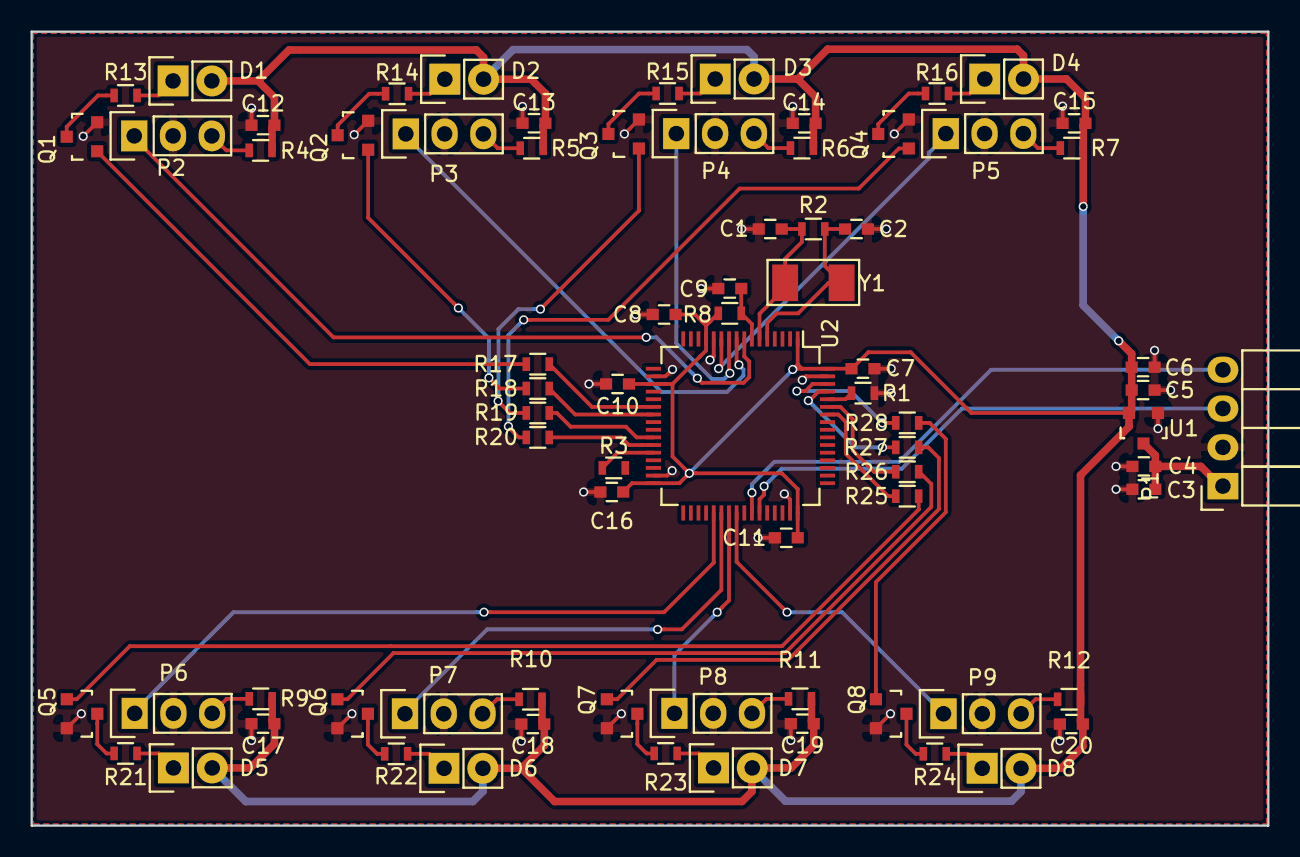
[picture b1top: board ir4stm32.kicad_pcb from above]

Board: 2 copper layers, 81.0 x 52.0 mm, 76 parts (0 on the bottom side), 58 nets.

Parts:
C1, C2: 20pF; C_0603
C3, C6: 106; C_0603
C4, C5, C7, C8, C9, C10, C11, C12, C13, C14, C15, C16, C17, C18, C19, C20: 104; C_0603
D1: IrDA_CH1; Socket_Strip_Straight_1x02
D2: IrDA_CH2; Socket_Strip_Straight_1x02
D3: IrDA_CH3; Socket_Strip_Straight_1x02
D4: IrDA_CH4; Socket_Strip_Straight_1x02
D5: IrDA_CH5; Socket_Strip_Straight_1x02
D6: IrDA_CH6; Socket_Strip_Straight_1x02
D7: IrDA_CH7; Socket_Strip_Straight_1x02
D8: IrDA_CH8; Socket_Strip_Straight_1x02
P1: + - R T; Socket_Strip_Angled_1x04
P2, P3, P4, P5, P6, P7, P8, P9: Socket_Strip_Straight_1x03
Q1, Q2, Q3, Q4, Q5, Q6, Q7, Q8: SS8050; SOT-23
R1, R3, R8: 10K; R_0603
R2: 1M; R_0603
R4, R5, R6, R7, R9, R10, R11, R12: 100; R_0603
R13, R14, R15, R16, R21, R22, R23, R24: 5R; R_0603
R17, R18, R19, R20, R25, R26, R27, R28: 1K; R_0603
U1: XC6206P332MR; SOT-23
U2: STM32F103RCT6; LQFP-64_10x10mm_Pitch0.5mm
Y1: X50328MSD2GC; SMD-5032

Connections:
3V3: C5.1, C6.1, C7.2, C8.1, C10.1, C11.2, C12.2, C13.2, C14.2, C15.2, C16.1, C17.2, C18.2, C19.2, C20.2, D1.2, D2.2, D3.2, D4.2, D5.2, D6.2, D7.2, D8.2, R4.2, R5.2, R6.2, R7.2, R8.1, R9.2, R10.2, R11.2, R12.2, U1.2, U2.1, U2.13, U2.19, U2.32, U2.48, U2.64
+5V: C3.1, C4.1, P1.1, U1.3
BOOT0: R1.2, U2.60
BOOT1: R3.2, U2.28
GND: C1.2, C2.2, C3.2, C4.2, C5.2, C6.2, C7.1, C8.2, C9.2, C10.2, C11.1, C12.1, C13.1, C14.1, C15.1, C16.2, C17.1, C18.1, C19.1, C20.1, P1.2, P2.2, P3.2, P4.2, P5.2, P6.2, P7.2, P8.2, P9.2, Q1.2, Q2.2, Q3.2, Q4.2, Q5.2, Q6.2, Q7.2, Q8.2, R1.1, U1.1, U2.12, U2.18, U2.31, U2.47, U2.63
IRIN_1: P2.1, U2.8
IRIN_2: P3.1, U2.9
IRIN_3: P4.1, U2.10
IRIN_4: P5.1, U2.11
IRIN_5: P6.1, U2.37
IRIN_6: P7.1, U2.38
IRIN_7: P8.1, U2.39
IRIN_8: P9.1, U2.40
unnamed: D1.1, R13.1
unnamed: D2.1, R14.1
unnamed: D3.1, R15.1
unnamed: D4.1, R16.1
unnamed: D5.1, R21.1
unnamed: D6.1, R22.1
unnamed: D7.1, R23.1
unnamed: D8.1, R24.1
unnamed: P2.3, R4.1
unnamed: P3.3, R5.1
unnamed: P4.3, R6.1
unnamed: P5.3, R7.1
unnamed: P6.3, R9.1
unnamed: P7.3, R10.1
unnamed: P8.3, R11.1
unnamed: P9.3, R12.1
unnamed: Q1.1, R17.1
unnamed: Q1.3, R13.2
unnamed: Q2.1, R18.1
unnamed: Q2.3, R14.2
unnamed: Q3.1, R19.1
unnamed: Q3.3, R15.2
unnamed: Q4.1, R20.1
unnamed: Q4.3, R16.2
unnamed: Q5.1, R25.1
unnamed: Q5.3, R21.2
unnamed: Q6.1, R26.1
unnamed: Q6.3, R22.2
unnamed: Q7.1, R27.1
unnamed: Q7.3, R23.2
unnamed: Q8.1, R28.1
unnamed: Q8.3, R24.2
OSCIN: C2.1, R2.1, U2.5, Y1.2
OSCOUT: C1.1, R2.2, U2.6, Y1.1
PWM1: R17.2, U2.22
PWM2: R18.2, U2.23
PWM3: R19.2, U2.26
PWM4: R20.2, U2.27
PWM5: R25.2, U2.58
PWM6: R26.2, U2.59
PWM7: R27.2, U2.61
PWM8: R28.2, U2.62
RESET: C9.1, R8.2, U2.7
RX1: P1.3, U2.43
TX1: P1.4, U2.42

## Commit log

2017-04-06 First Blood
2017-04-06 feat: ...
2017-04-07 feat: Remove some useless functions
2017-04-09 feat: A little bit enhancement about NVIC config
2017-04-09 doc: (readme)
2017-04-09 feat: (EXTI) Success, but still have some trouble with interrupt handle of UART
2017-04-09 fix: Try to figure out ...
2017-04-09 fix: Interrupt working both EXTI and USART
2017-04-12 mod: RTSR -> FTSR
2017-04-14 fix: (GPIO) Input Mode
2017-04-14 doc: Add Comments
2017-04-14 feat: Hardware
2017-04-15 feat: Unit test
2017-04-15 feat: A little bit enhancement
2017-04-15 fix: Syntax erro
2017-04-16 style: (num2char) A little bit enhancement
2017-04-16 feat: (uart_num2char) Support Unsigned int (Max: 4294967295)
2017-04-17 feat: (irda_decode) Struct
2017-04-17 feat: (decode) (delay)
2017-04-17 feat: (decode) Add delay function to escape the 38khz wave
2017-04-17 doc: Schedule
2017-04-17 feat: Decode Success
2017-04-17 fix: Syntax Error
2017-04-18 feat: Gerber files
2017-04-18 feat: Translate Position file
2017-04-18 fix: (BOM)
2017-04-18 doc: Position
2017-04-18 Clean
2017-04-18 doc: Before Translate
2017-04-18 doc: After Translate
2017-04-18 fix: (#Y1)Add Spot, Clean
2017-04-18 fix: (Component missing) I forgot to update the attributes of the footprint to Normal + Insert
2017-04-18 feat: After decode
2017-04-18 doc: Final GERBER
2017-04-18 doc: PCB bom and smt position files
2017-04-18 feat: decode function will be return if the cache is Overflowed
2017-04-19 feat: (decode) Rewrite decode function, and rename 'TOKEN_NUM'
2017-04-19 fix: (Syntax Error) typo
2017-04-19 fix: Logic Error
2017-04-19 refactor: (Statements)
2017-04-19 refactor: (global variables)
2017-04-19 feat: (EXTI2_IRQHandler) Logic
2017-04-21 feat: A lot of new features...
2017-04-24 fix: BOOT Options error
2017-04-24 style: CVS Translate
2017-04-26 feat: (irda_encode) add a new function, and some comments
2017-04-26 feat: (uart_decode) Handle Send Data Command
2017-04-26 fix: (uart_decode) incompatible type for argument of irda_encode()
2017-05-02 feat: (bit band) Enhancement
2017-05-07 feat: (bit_band) Enhancement
2017-05-07 fix: (GPIO Config)
2017-05-07 release: (unit test)
2017-05-07 fix: Register Config Error
2017-05-07 fix: (EXTI 9-5)
2017-05-08 feat: (PWM) Final commit
2017-05-08 feat: (PWM) Commented-Out Code
2017-05-22 fix: (PWM) Add CCR Config
2017-05-22 fix: (Encode) Make sure current PWM channel will be disable
2017-05-22 fix: (oop) IrPWM Bitband Error
2017-05-22 feat: (uart) Delete key feedback
2017-05-22 doc: (comments)
2017-05-22 feat: (uart) Enhancement
2017-05-23 doc: (Sche) Detail
2017-05-23 fix: (Images) Path
2017-05-23 fix: (doc) Index
2017-05-24 doc: Update
2017-05-24 fix: typo
2017-05-25 final Update ?
2017-05-30 doc: Paper
2017-05-30 cod: Images
2017-12-17 fix: (Image) Path typo
2020-08-10 [ImgBot] Optimize images
    *Total -- 2,755.95kb -> 2,076.58kb (24.65%)
    /libs/STM32_USB-FS-Device_Lib_V4.0.0/_htmresc/bulb16.gif -- 0.84kb -> 0.16kb (81.21%)
    /libs/STM32_USB-FS-Device_Lib_V4.0.0/_htmresc/ar_s.gif -- 0.86kb -> 0.17kb (79.75%)
    /libs/STM32_USB-FS-Device_Lib_V4.0.0/Libraries/CMSIS/Documentation/RTOS/html/MailQueue.png -- 14.39kb -> 5.77kb (59.93%)
    /libs/STM32_USB-FS-Device_Lib_V4.0.0/Libraries/CMSIS/Documentation/RTOS/html/MessageQueue.png -- 11.62kb -> 5.05kb (56.57%)
    /libs/STM32_USB-FS-Device_Lib_V4.0.0/Libraries/CMSIS/Documentation/RTOS/html/CMSIS_RTOS_Files.png -- 15.34kb -> 8.05kb (47.52%)
